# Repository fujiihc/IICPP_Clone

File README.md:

# IICPP_Clone
Mark IIC+/++ Inspired Clone

## Overview
This goal of this project was to create a reasonably accurate "clone" of the Mesa Boogie Mark IIC+/++ Tube Amplifier. 
I was inspired by my love of Metallica and James Hetfield's rhythm playing, as well as my fascination with audio electronics.

These amplifiers can be considered legendary and are the subject of many discussions on what makes them so special and highly sought after.
Although a legitimate Mark IIC+ Reissue exists, as do many originals, these amps are often expensive, and vary in their component and feature choices.
I wouldn't consider this version to be a 100% perfect clone as there is not much accurate, detailed information on these amplifiers, and some of the schematics that are available have been noted to be incorrect. Certain components are also not readily available today, and so some design concessions have to be made. Modifications due to limited design information, component availability, limited budget, and design complexity were made. However, the core DNA and design choices of the original were followed as closely as possible and I  would consider this a reasonably faithful clone.
By having a more accessible, afforable, and reasonably accurate version, hopefully I can help contribute to others' tone chasing journeys, or help demystify (in some capacity) what makes these amps so special.

I currently do not own any Mesa Boogie amplifiers to base these designs off of. Instead, I have researched this amp in depth, scouring the internet for schematics, gut shots, and getting advice from others who have successfully built their own clones or similar amplifiers. 

A major goal of this project is to stay under a budget of $1800 (Half the price of a Reissue).

An important note, this project is for educational purposes and personal use only, and this repository is for documenting my learning progress and findings. I have no affiliation with Mesa Boogie or any sort of company or anything like that. I just like making stuff and playing guitar. Please don't sue me :)

## Table of Contents 
  **PROJECTS WERE CREATED IN KICAD 9.0**
  - [Custom Libraries](/Custom%20Libraries): Contains Custom Footprints for Parts Not Available from KICAD Default Libraries.
  - [Experiments](/Experiments): Contains Experimental Layouts and Ideas That Haven't Been Confirmed/Finalized.
  - [Graphic EQ](/Graphic%20EQ): Contains KICAD Projects with Schematics, PCB Designs, and Gerber Files for 5-Band EQ Driver and Slider Boards.
  - [Images](/Images): Contains Images for Various README's.
  - [Power Amp](/Power%20Amp): Contains KICAD Projects with Schematics, PCB Designs, and Gerber Files for Power Amp Boards.
  - [Power Supply](/Power%20Supply): Contains KICAD Projects with Schematics, PCB Designs, and Gerber Files for Power Supply Boards.
  - [Preamp](/Preamp): Contains KICAD Projects with Schematics, PCB Designs, and Gerber Files for Preamp Boards.

## Organizational/Research Spreadsheet
Contains Research Links, Bill of Materials, Instructions, Personal Findings, Notes, etc.
 - [Link to Google Sheet](https://docs.google.com/spreadsheets/d/1ZE0vuGfygjLFiTaHai0WybOM6v7LY0qXNIPXHzz1JHo/edit?usp=sharing)

## Google Drive
Contains Pictures, Schematics, Datasheets, Manuals, Etc. Just useful information I found along the way.
 - [Link to Google Drive](https://drive.google.com/drive/folders/1geqLoLI9ncoWVvD1H8Yl4hjtfwfBTIB6?usp=drive_link)

## Thank You's
The following people have been invaluable in the progress of this project, both directly and indirectly. Whether they posted schematics that they traced, or in-depth gut shots or photos of their own builds, or even answered my questions when I ran into roadblocks, I would like to thank them. I wouldn't have made this much progress without them:

  - [JAY OMEGA](https://boogieforum.com/members/jay-omega.83481/)

  - [JRB32](https://boogieforum.com/members/jrb32.41252/)

  - [DANO](https://boogieforum.com/members/dan__o.6723/)

  - [DANN VALENTINO](https://www.facebook.com/dann.valentino/)

  - [MATADOR](https://boogieforum.com/members/matador.84058/)

## To-Do/Future Plans

  - Create Modified C++ Compatible Preamp Board With Reverb
  - Create Modified C++ Compatible Preamp Board Without Reverb
  - Create Power Amp Board
  - Create Public Google Drive with Helpful Files (Pictures, Schematics, Datasheets, Manuals, Etc).

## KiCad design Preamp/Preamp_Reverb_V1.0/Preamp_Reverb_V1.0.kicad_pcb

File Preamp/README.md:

# Preamp

## Overview
The Preamp for the IICPP has two switchable modes, Clean and Lead. There are also various Pull-Potentiometer/Switch Activated modes for tone shaping. 

It's important to note that the Tone Stack for the IICPP comes after the First Gain Stage, and before all the Following Gain Stages.
An optional mod for the IICPP is the "C++" Mod, which adds a little bit more gain on tap. This is an optional mod, but also switchable when implemented.

There are two versions of the Preamp here, one which has Reverb (R) and one with No Reverb (NR). the Reverb, when implemented, is footswitchable. The No Reverb version uses one less 12AX7 Preamp Tube, and uses fewer components as well.
The rest of the components and the schematic are the same.

## Status
  - 

## Bill Of Materials
  - [Link to Google Sheet](https://docs.google.com/spreadsheets/d/1ZE0vuGfygjLFiTaHai0WybOM6v7LY0qXNIPXHzz1JHo/edit?gid=1339717624#gid=1339717624)

## Notes
  - 
## To-Do/Future Plans
  - 
## Images

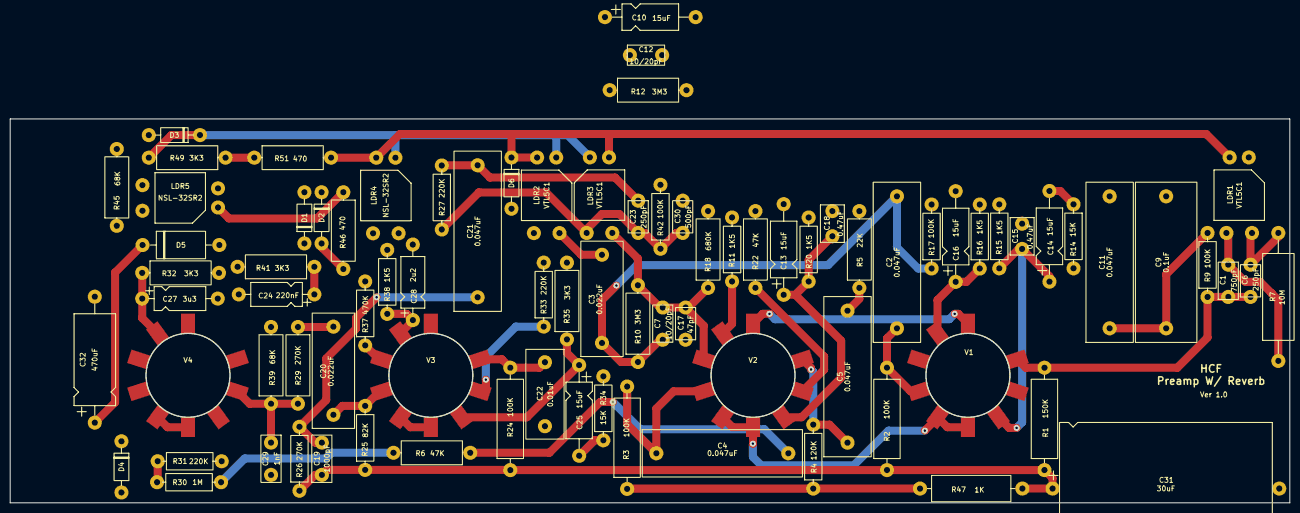
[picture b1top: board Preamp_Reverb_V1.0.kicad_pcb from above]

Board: 2 copper layers, 254.0 x 76.2 mm, 84 parts (0 on the bottom side), 47 nets.

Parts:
C1: 750pF; 20_750pF_1KV_Cer_7.4_4.0_.6.4
C2, C4, C5, C11, C21: 0.047uF; 715P47354LAD3
C3, C20: 0.022uF; 715P22354KAD3
C6, C23: 250pF; 10_47_120_180_250_500pF_1KV_Cer_6.4_4.0_6.4
C7, C12: 10/20pF; 20_750pF_1KV_Cer_7.4_4.0_.6.4
C9: 0.1uF; 715P10454LAD3
C10, C13, C14, C16, C25: 15uF; CP_Axial_L11.0mm_D5.0mm_P18.00mm_Horizontal
C15, C18: 0.47uF; C_Rect_L7.2mm_W4.5mm_P5.00mm_FKS2_FKP2_MKS2_MKP2
C17: 47pF; 10_47_120_180_250_500pF_1KV_Cer_6.4_4.0_6.4
C19: 1000pF; 1000pF_1KV_Cer_9.4_4.0_6.4
C22: 0.01uF; 715P10354JAD3
C24: 220nF; CP_Axial_L10.0mm_D4.5mm_P15.00mm_Horizontal
C27: 3u3; CP_Axial_L10.0mm_D4.5mm_P15.00mm_Horizontal
C28: 2u2; CP_Axial_L10.0mm_D4.5mm_P15.00mm_Horizontal
C29: 1nF; 1000pF_1KV_Cer_9.4_4.0_6.4
C30: 500pF; 10_47_120_180_250_500pF_1KV_Cer_6.4_4.0_6.4
C31: 30uF; CP_Axial_L42.0mm_D26.0mm_P45.00mm_Horizontal
C32: 470uF; CP_Axial_L18.0mm_D8.0mm_P25.00mm_Horizontal
D1, D6: 6V 1W; D_DO-41_SOD81_P10.16mm_Horizontal
D2, D3, D4: 1N4006; D_DO-41_SOD81_P10.16mm_Horizontal
D5: 1N5352BRL; D_DO-201_P15.24mm_Horizontal
LDR1, LDR2, LDR3: VTL5C1; PerkinElmer_VTL5C
LDR4, LDR5: NSL-32SR2; PerkinElmer_VTL5C
R1: 150K; R_Axial_DIN0516_L15.5mm_D5.0mm_P20.32mm_Horizontal
R2, R3, R24: 100K; R_Axial_DIN0516_L15.5mm_D5.0mm_P20.32mm_Horizontal
R4: 120K; R_Axial_DIN0309_L9.0mm_D3.2mm_P12.70mm_Horizontal
R5: 22K; R_Axial_DIN0414_L11.9mm_D4.5mm_P15.24mm_Horizontal
R6, R22: 47K; R_Axial_DIN0414_L11.9mm_D4.5mm_P15.24mm_Horizontal
R7: 10M; R_Axial_DIN0617_L17.0mm_D6.0mm_P25.40mm_Horizontal
R9, R17, R42: 100K; R_Axial_DIN0309_L9.0mm_D3.2mm_P12.70mm_Horizontal
R10, R12: 3M3; R_Axial_DIN0414_L11.9mm_D4.5mm_P15.24mm_Horizontal
R11, R15, R16, R20, R38: 1K5; R_Axial_DIN0309_L9.0mm_D3.2mm_P12.70mm_Horizontal
R14, R34: 15K; R_Axial_DIN0309_L9.0mm_D3.2mm_P12.70mm_Horizontal
R18: 680K; R_Axial_DIN0414_L11.9mm_D4.5mm_P15.24mm_Horizontal
R25: 82K; R_Axial_DIN0309_L9.0mm_D3.2mm_P12.70mm_Horizontal
R26: 270K; R_Axial_DIN0309_L9.0mm_D3.2mm_P12.70mm_Horizontal
R27, R31, R33: 220K; R_Axial_DIN0309_L9.0mm_D3.2mm_P12.70mm_Horizontal
R29: 270K; R_Axial_DIN0414_L11.9mm_D4.5mm_P15.24mm_Horizontal
R30: 1M; R_Axial_DIN0309_L9.0mm_D3.2mm_P12.70mm_Horizontal
R32, R35, R41, R49: 3K3; R_Axial_DIN0414_L11.9mm_D4.5mm_P15.24mm_Horizontal
R37: 470K; R_Axial_DIN0309_L9.0mm_D3.2mm_P12.70mm_Horizontal
R39, R45: 68K; R_Axial_DIN0414_L11.9mm_D4.5mm_P15.24mm_Horizontal
R46, R51: 470; R_Axial_DIN0414_L11.9mm_D4.5mm_P15.24mm_Horizontal
R47: 1K; R_Axial_DIN0516_L15.5mm_D5.0mm_P20.32mm_Horizontal
V1, V2, V3, V4: 12AX7; VT9-ST-C

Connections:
D: R3.1, R4.1, R47.1
E: C19.1, C31.1, R1.1, R2.1, R24.1, R25.1, R26.1, R47.2
GEQ: LDR5.3, R45.1
GND: C15.2, C16.2, C17.2, C18.2, C27.2, C28.2, C29.2, C30.2, C31.2, C32.2, D1.2 (A), D5.2 (A), D6.2 (A), LDR4.3, LDR5.4, R11.2, R14.2, R15.2, R16.2, R17.2, R18.2, R20.2, R22.2, R31.2, R32.2, R33.2, R34.2, R35.2, R37.2, R38.2, R39.2, R41.2, R42.2, R45.2
LDR1+: D6.1 (K), LDR1.2 (+), LDR2.2 (+), LDR3.2 (+), LDR4.2 (+), R51.2
LDR2-: D3.1 (K), LDR2.1 (-), LDR3.1 (-), LDR4.1 (-), R49.2
Lead In: C3.2, LDR2.3
Lead Out: C7.2, C17.1, LDR3.4, R10.2, R18.1, V2.7 (G)
unnamed: C1.2, LDR1.4, R7.1
unnamed: C2.2, C3.1, C7.1, R10.1, R12.1, R17.1
unnamed: C4.2, R6.1
unnamed: C5.2, R5.1
unnamed: C6.2, LDR1.3, R7.2
unnamed: C9.1, C11.1, R9.2
unnamed: C12.1, R12.2
unnamed: C20.2, R29.1
unnamed: C21.2, C23.1, R27.1
unnamed: C23.2, C30.1, LDR3.3, R27.2, R42.1
unnamed: C25.2, R34.1
unnamed: D1.1 (K), LDR5.2 (+)
unnamed: D2.2 (A), R46.2
unnamed: C32.1, D5.1 (K), R49.1, R51.1
unnamed: LDR5.1 (-), R46.1
unnamed: C14.2, R14.1
unnamed: C2.1, R2.2, V1.6 (A)
unnamed: C16.1, R16.1, V1.8 (K)
unnamed: C1.1, C6.1, R1.2, R9.1, V1.1 (A)
unnamed: C14.1, C15.1, R15.1, V1.3 (K)
unnamed: V1.4 (F1), V1.5 (F1), V2.4 (F1), V2.5 (F1), V3.4 (F1), V3.5 (F1), V4.4 (F1), V4.5 (F1)
unnamed: V1.9 (F2), V2.9 (F2), V3.9 (F2), V4.9 (F2)
unnamed: C4.1, R3.2, V2.6 (A)
unnamed: C10.1, R11.1, V2.8 (K)
unnamed: C5.1, R4.2, V2.1 (A)
unnamed: R22.1, V2.2 (G)
unnamed: C13.1, C18.1, R20.1, V2.3 (K)
unnamed: C20.1, R25.2, V3.6 (A)
unnamed: R37.1, V3.7 (G)
unnamed: C28.1, R38.1, V3.8 (K)
unnamed: C22.1, R24.2, V3.1 (A)
unnamed: C25.1, R35.1, V3.3 (K)
unnamed: R30.2, R31.1, V4.7 (G)
unnamed: C27.1, R32.1, V4.8 (K)
unnamed: C19.2, C21.1, R26.2, V4.1 (A)
unnamed: C29.1, R29.2, R39.1, V4.2 (G)
unnamed: C24.1, R41.1, V4.3 (K)
Reverb In: R6.2, R30.1
Tank Out: R33.1, V3.2 (G)

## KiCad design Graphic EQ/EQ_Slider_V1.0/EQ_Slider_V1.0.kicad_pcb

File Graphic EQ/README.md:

# Graphic EQ

## Overview
The 5-Band Graphic Equalizer for the IICPP consists of two parts, the EQ Driver and the EQ Slider Board. 

In conjunction, they can boost or cut frequencies at 80Hz, 240Hz, 750Hz, 2200Hz and 6600Hz.

The GEQ can be engaged in EQ Out, EQ In, and EQ Auto Modes, and can be footswitched.

EQ Out has the GEQ Off, EQ In has the GEQ In for Lead and Clean Modes, and EQ Auto engages the EQ when Lead is engaged.

## Status
  - Schematics, PCB Designs, and Gerbers for V1.0 of both the Driver and Slider Boards are Complete.
  - Gerbers generated for JLCPCB Manufacturing.

## Bill Of Materials
  - [Link to Google Sheet](https://docs.google.com/spreadsheets/d/1ZE0vuGfygjLFiTaHai0WybOM6v7LY0qXNIPXHzz1JHo/edit?gid=0#gid=0)

## Notes
  - MPSA70 is discontinued.
    - Options are NOS, finding drop-in replacement, or finding suitable alternatives for ALL transistors.
  - T322/T110 Tantalum Caps are expensive.
    - T322/T110 were used in some originals, but Cheaper Tant Caps (T356), Film Caps, or Orange Drop Caps also apparently work.
    
## To-Do/Future Plans
  - Order V1.0 Boards
  - Find Suitable Transistor Replacements

## Images
Slider V1.0:

Driver V1.0:

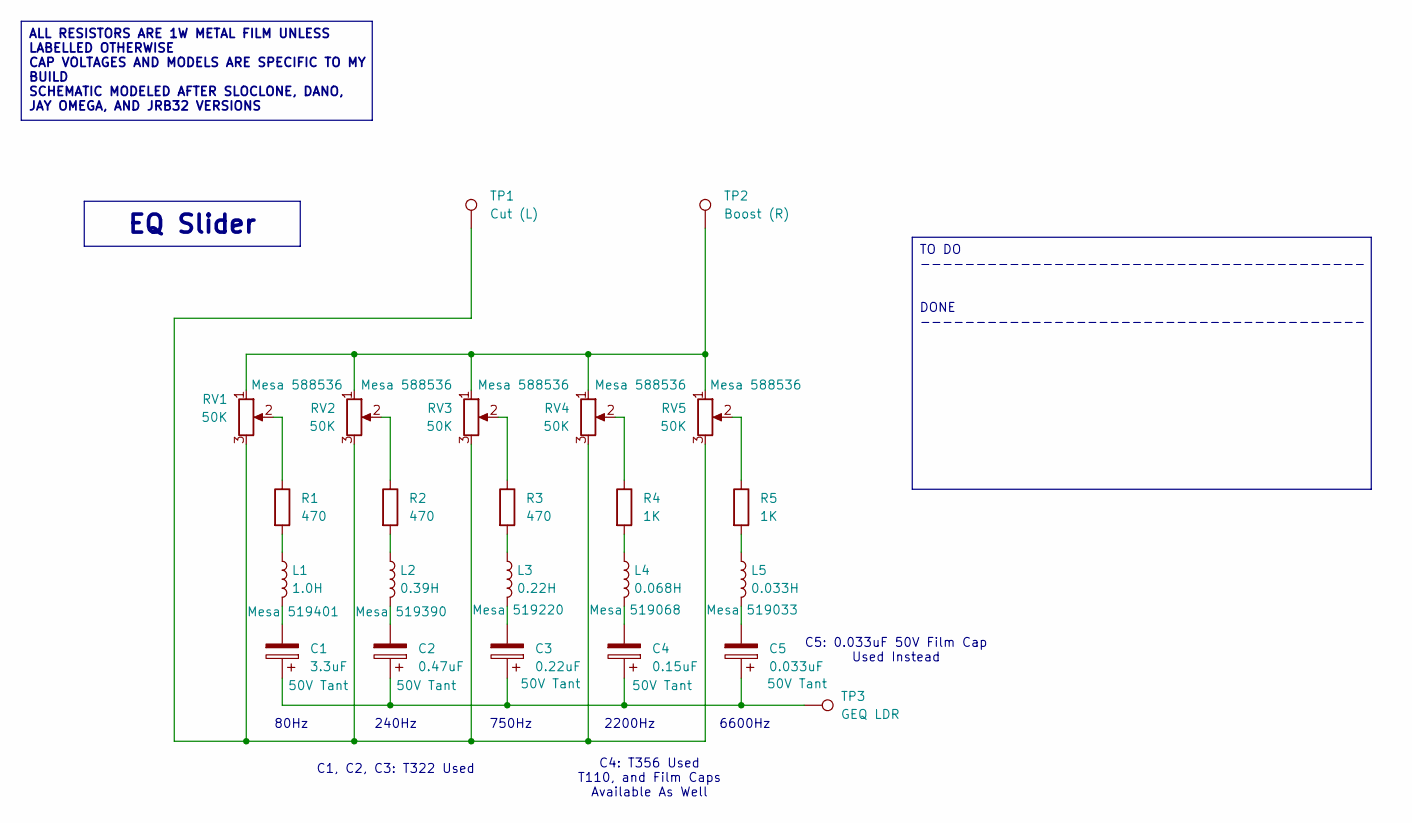
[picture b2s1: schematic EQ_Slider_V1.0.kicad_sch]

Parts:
C1: 3.3uF; CP_Axial_L11.0mm_D5.0mm_P18.00mm_Horizontal
C2: 0.47uF; CP_Axial_L10.0mm_D4.5mm_P15.00mm_Horizontal
C3: 0.22uF; CP_Axial_L10.0mm_D4.5mm_P15.00mm_Horizontal
C4: 0.15uF; CP_Radial_Tantal_D4.5mm_P5.00mm
C5: 0.033uF; C_Rect_L7.2mm_W2.5mm_P5.00mm_FKS2_FKP2_MKS2_MKP2
L1: 1.0H; MB Inductor
L2: 0.39H; MB Inductor
L3: 0.22H; MB Inductor
L4: 0.068H; MB Inductor
L5: 0.033H; MB Inductor
R1, R2, R3: 470; R_Axial_DIN0414_L11.9mm_D4.5mm_P15.24mm_Horizontal
R4, R5: 1K; R_Axial_DIN0414_L11.9mm_D4.5mm_P15.24mm_Horizontal
RV1, RV2, RV3, RV4, RV5: 50K; Mesa 588536
TP1: Cut (L); Out_Hole_3.4_1.8
TP2: Boost (R); Out_Hole_3.4_1.8
TP3: GEQ LDR; Out_Hole_3.4_1.8

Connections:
unnamed: C1.1, C2.1, C3.1, C4.1, C5.1, TP3.1
unnamed: C1.2, L1.2
unnamed: C2.2, L2.2
unnamed: C3.2, L3.2
unnamed: C4.2, L4.2
unnamed: C5.2, L5.2
unnamed: L1.1, R1.2
unnamed: L2.1, R2.2
unnamed: L3.1, R3.2
unnamed: L4.1, R4.2
unnamed: L5.1, R5.2
unnamed: R1.1, RV1.2
unnamed: R2.1, RV2.2
unnamed: R3.1, RV3.2
unnamed: R4.1, RV4.2
unnamed: R5.1, RV5.2
unnamed: RV1.1, RV2.1, RV3.1, RV4.1, RV5.1, TP2.1
unnamed: RV1.3, RV2.3, RV3.3, RV4.3, RV5.3, TP1.1

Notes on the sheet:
C5: 0.033uF 50V Film Cap Used Instead
750Hz
80Hz
240Hz
6600Hz
C4: T356 Used T110, and Film Caps Available As Well
2200Hz
C1, C2, C3: T322 Used
ALL RESISTORS ARE 1W METAL FILM UNLESS LABELLED OTHERWISE CAP VOLTAGES AND MODELS ARE SPECIFIC TO MY BUILD SCHEMATIC MODELED AFTER SLOCLONE, DANO, JAY OMEGA, AND JRB32 VERSIONS
TO DO ---------------------------------------- DONE ----------------------------------------
EQ Slider

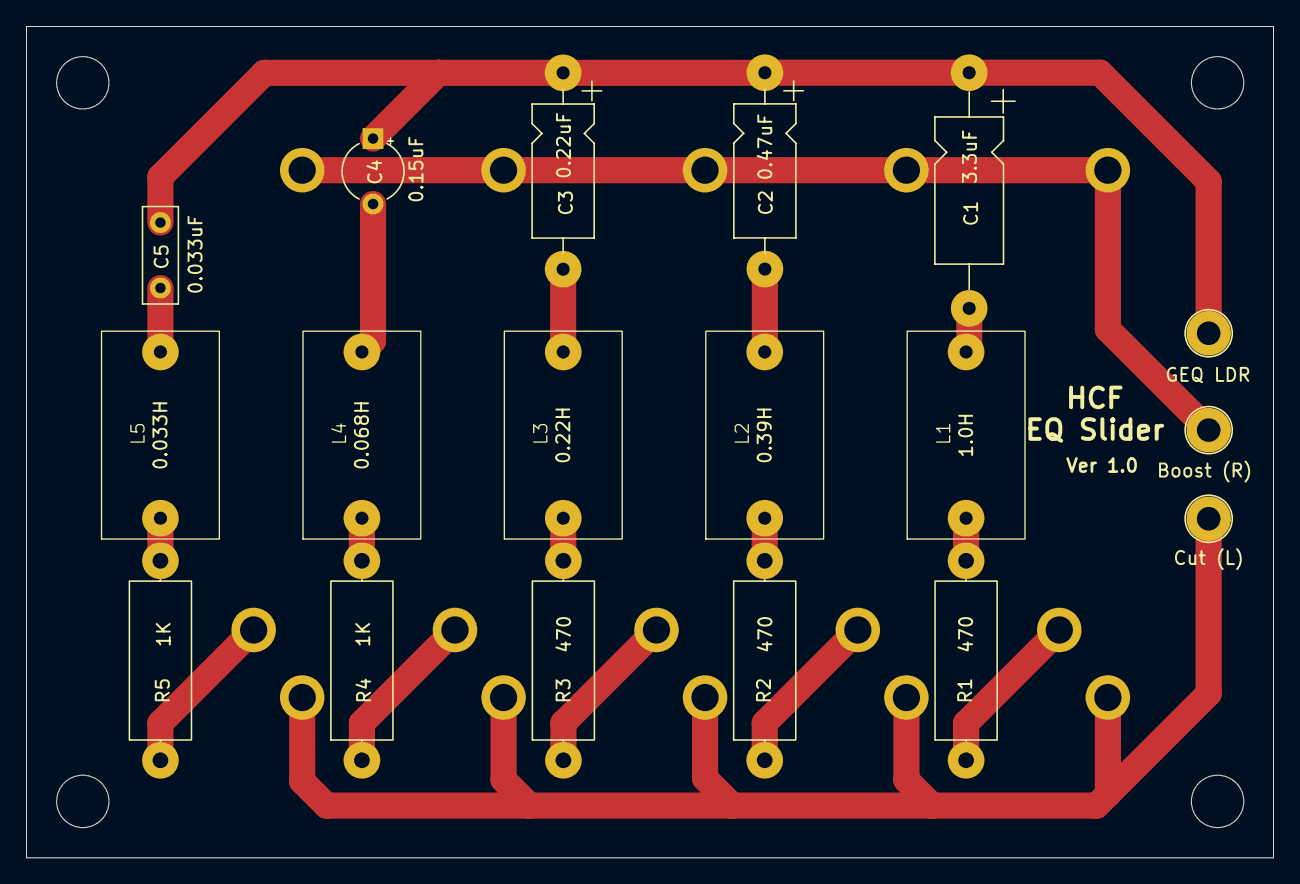
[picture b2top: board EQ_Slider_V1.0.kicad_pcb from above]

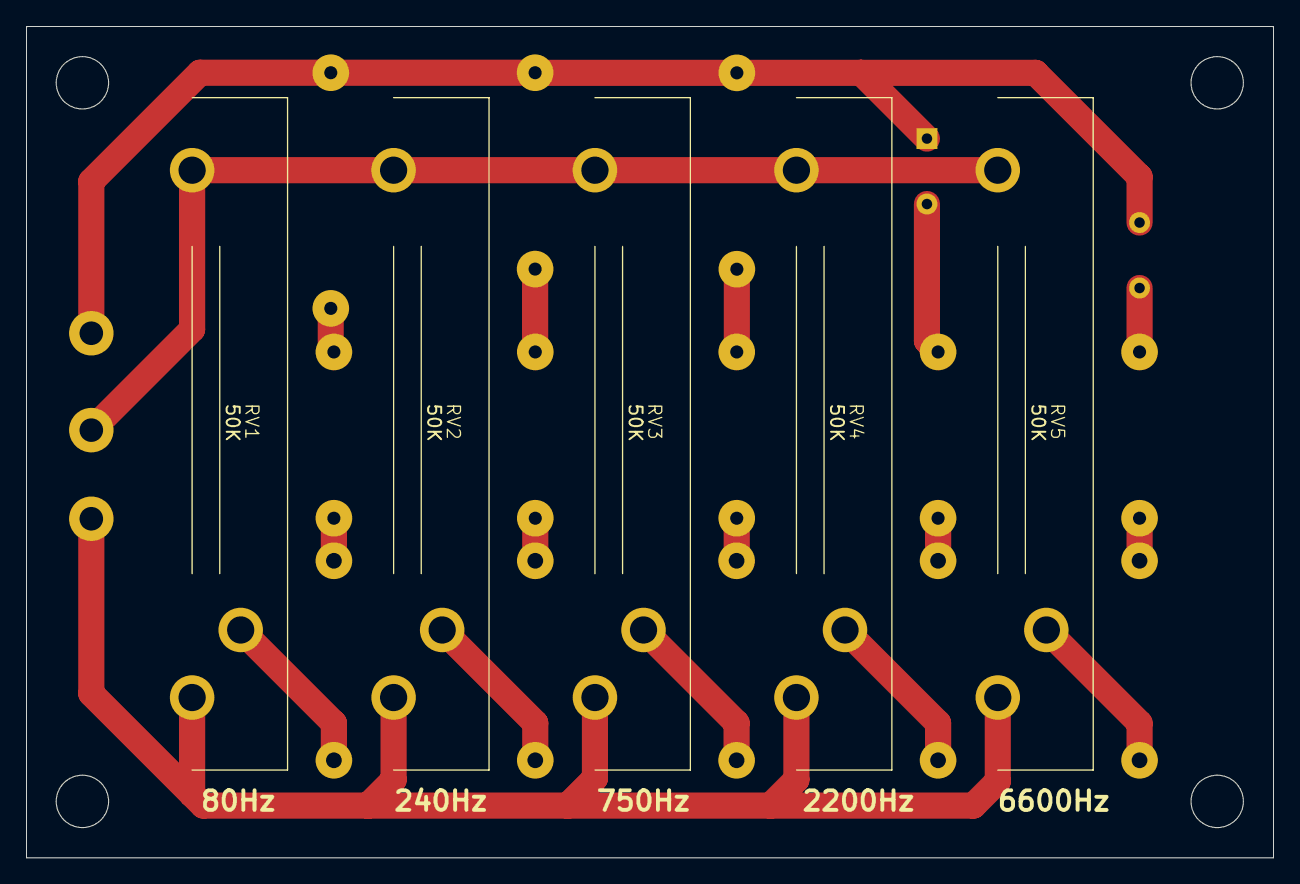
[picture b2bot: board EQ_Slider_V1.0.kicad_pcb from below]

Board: 2 copper layers, 95.3 x 63.5 mm, 23 parts (5 on the bottom side), 18 nets.

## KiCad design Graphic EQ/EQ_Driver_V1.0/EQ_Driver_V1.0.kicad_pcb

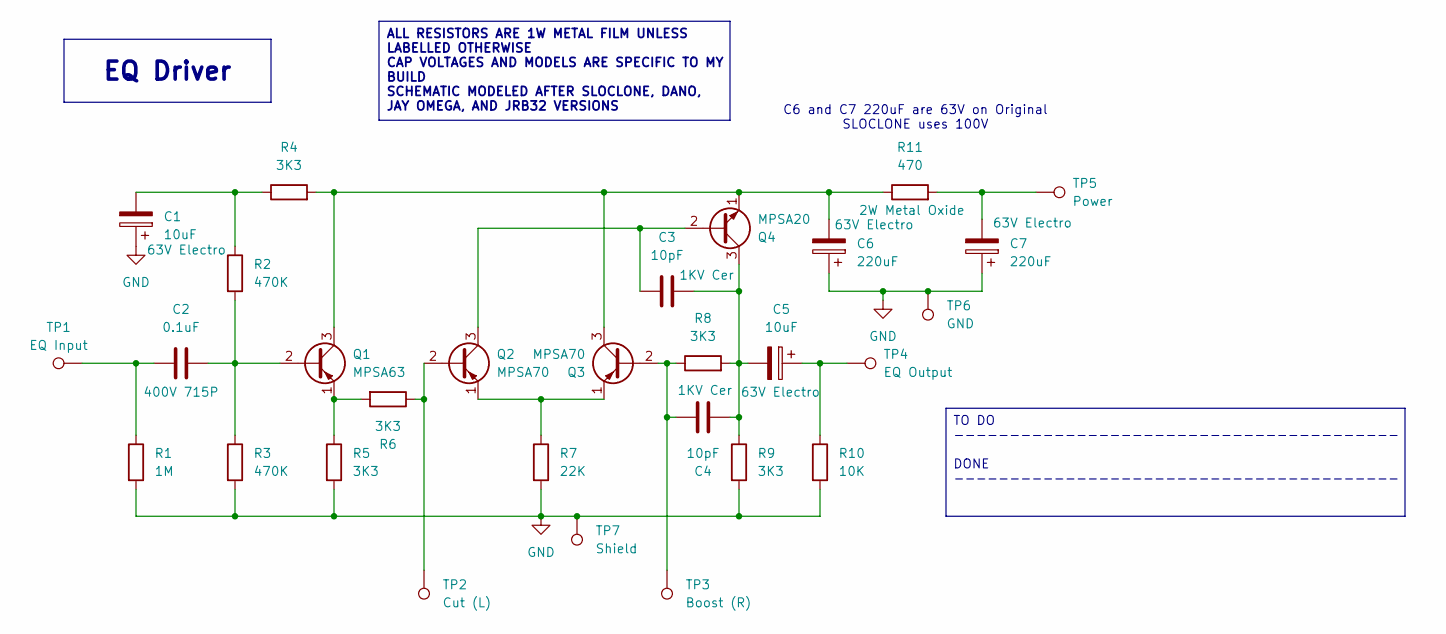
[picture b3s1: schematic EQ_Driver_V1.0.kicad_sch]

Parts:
C1, C5: 10uF; CP_Axial_L18.0mm_D6.5mm_P25.00mm_Horizontal
C2: 0.1uF; 715P10454LAD3
C3, C4: 10pF; 10_47_120_180_250_500pF_1KV_Cer_6.4_4.0_6.4
C6, C7: 220uF; CP_Axial_L25.0mm_D10.0mm_P30.00mm_Horizontal
Q1: MPSA63; TO-92_Wide
Q2, Q3: MPSA70; TO-92_Wide
Q4: MPSA20; TO-92_Wide
R1: 1M; R_Axial_DIN0309_L9.0mm_D3.2mm_P12.70mm_Horizontal
R2, R3: 470K; R_Axial_DIN0309_L9.0mm_D3.2mm_P12.70mm_Horizontal
R4, R5, R6, R8, R9: 3K3; R_Axial_DIN0414_L11.9mm_D4.5mm_P15.24mm_Horizontal
R7: 22K; R_Axial_DIN0414_L11.9mm_D4.5mm_P15.24mm_Horizontal
R10: 10K; R_Axial_DIN0309_L9.0mm_D3.2mm_P12.70mm_Horizontal
R11: 470; R_Axial_DIN0516_L15.5mm_D5.0mm_P20.32mm_Horizontal
TP1: EQ Input; WirePad
TP2: Cut (L); WirePad
TP3: Boost (R); WirePad
TP4: EQ Output; Out_Hole_3.4_1.8
TP5: Power; Out_Hole_3.4_1.8
TP6: GND; WirePad
TP7: Shield; WirePad

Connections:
GND: C1.1, C6.1, C7.1, R1.2, R3.2, R5.2, R7.2, R9.2, R10.2, TP6.1, TP7.1
unnamed: C1.2, R2.1, R4.1
unnamed: C2.1, R1.1, TP1.1
unnamed: C5.1, R10.1, TP4.1
unnamed: C7.2, R11.2, TP5.1
unnamed: C2.2, Q1.2 (B), R2.2, R3.1
unnamed: C6.2, Q1.3 (C), Q3.3 (C), Q4.1 (E), R4.2, R11.1
unnamed: Q1.1 (E), R5.1, R6.2
unnamed: Q2.2 (B), R6.1, TP2.1
unnamed: C3.1, Q2.3 (C), Q4.2 (B)
unnamed: Q2.1 (E), Q3.1 (E), R7.1
unnamed: C4.1, Q3.2 (B), R8.1, TP3.1
unnamed: C3.2, C4.2, C5.2, Q4.3 (C), R8.2, R9.1

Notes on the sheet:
C6 and C7 220uF are 63V on Original SLOCLONE uses 100V
EQ Driver
ALL RESISTORS ARE 1W METAL FILM UNLESS LABELLED OTHERWISE CAP VOLTAGES AND MODELS ARE SPECIFIC TO MY BUILD SCHEMATIC MODELED AFTER SLOCLONE, DANO, JAY OMEGA, AND JRB32 VERSIONS
TO DO ---------------------------------------- DONE ----------------------------------------

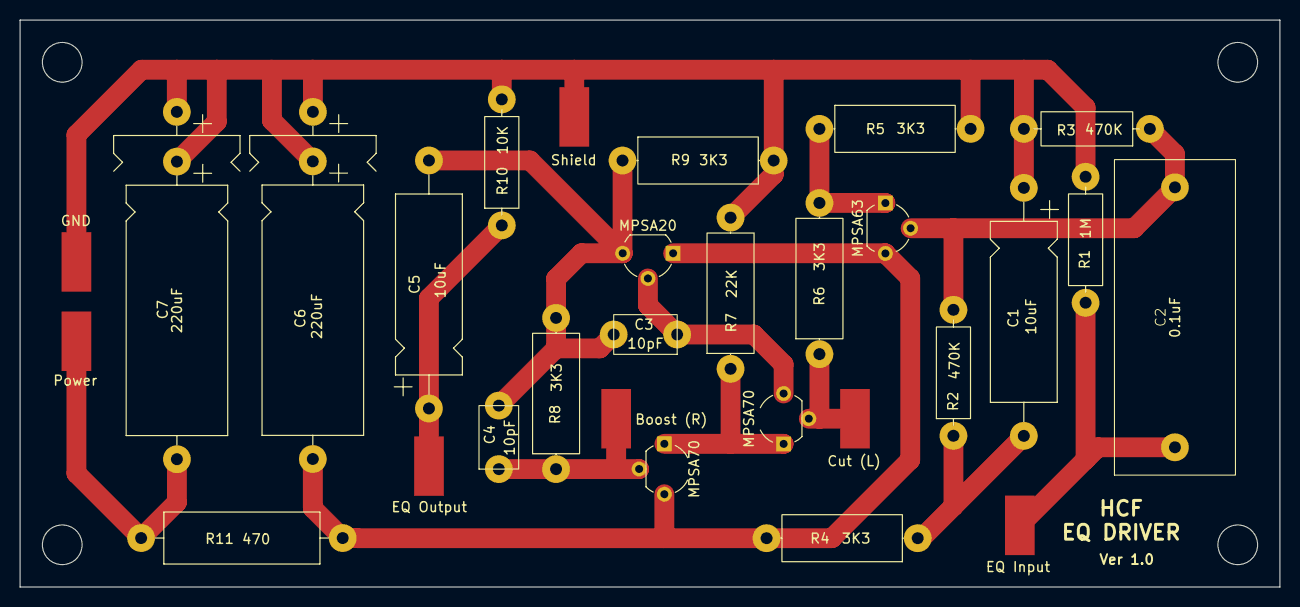
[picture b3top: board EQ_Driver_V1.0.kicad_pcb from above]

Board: 2 copper layers, 127.0 x 57.2 mm, 29 parts (0 on the bottom side), 13 nets.

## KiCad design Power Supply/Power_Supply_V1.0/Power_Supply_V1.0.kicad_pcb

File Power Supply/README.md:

# Power Supply

## Overview
The Power Supply for the IICPP contains the Main HT/B+ Taps as well as the Bias and Graphic EQ Power Supplies.

The board supports x2 (for 60W) and x4 (for 100W and Simul-Class) 300V 220uF Reservoir Caps.

## Status
  - Schematic, PCB Design, and Gerber for V1.0 of the Power Supply Board are Complete.
  - Gerbers generated for JLCPCB Manufacturing.

## Bill Of Materials
  - [Link to Google Sheet](https://docs.google.com/spreadsheets/d/1ZE0vuGfygjLFiTaHai0WybOM6v7LY0qXNIPXHzz1JHo/edit?gid=810989497#gid=810989497)

## Notes
  - Bias Supply for SLOCLONE/DANO, Mesa Boogie, and JRB32 Schematics are incorrect. The correct Bias Supply Schematic is used in this V1.0, which was traced from original IIB and IIC+ Power Supply Boards.
  - Validated/Correct and Incorrect Bias Supply Versions and Validation Sources can be found in [Experiments](../Experiments)
    
## To-Do/Future Plans
  - Add/Remove Taps based on Power Transformer. Currently looking at Hammond 291ZZ.

## Images
Power Supply V1.0:

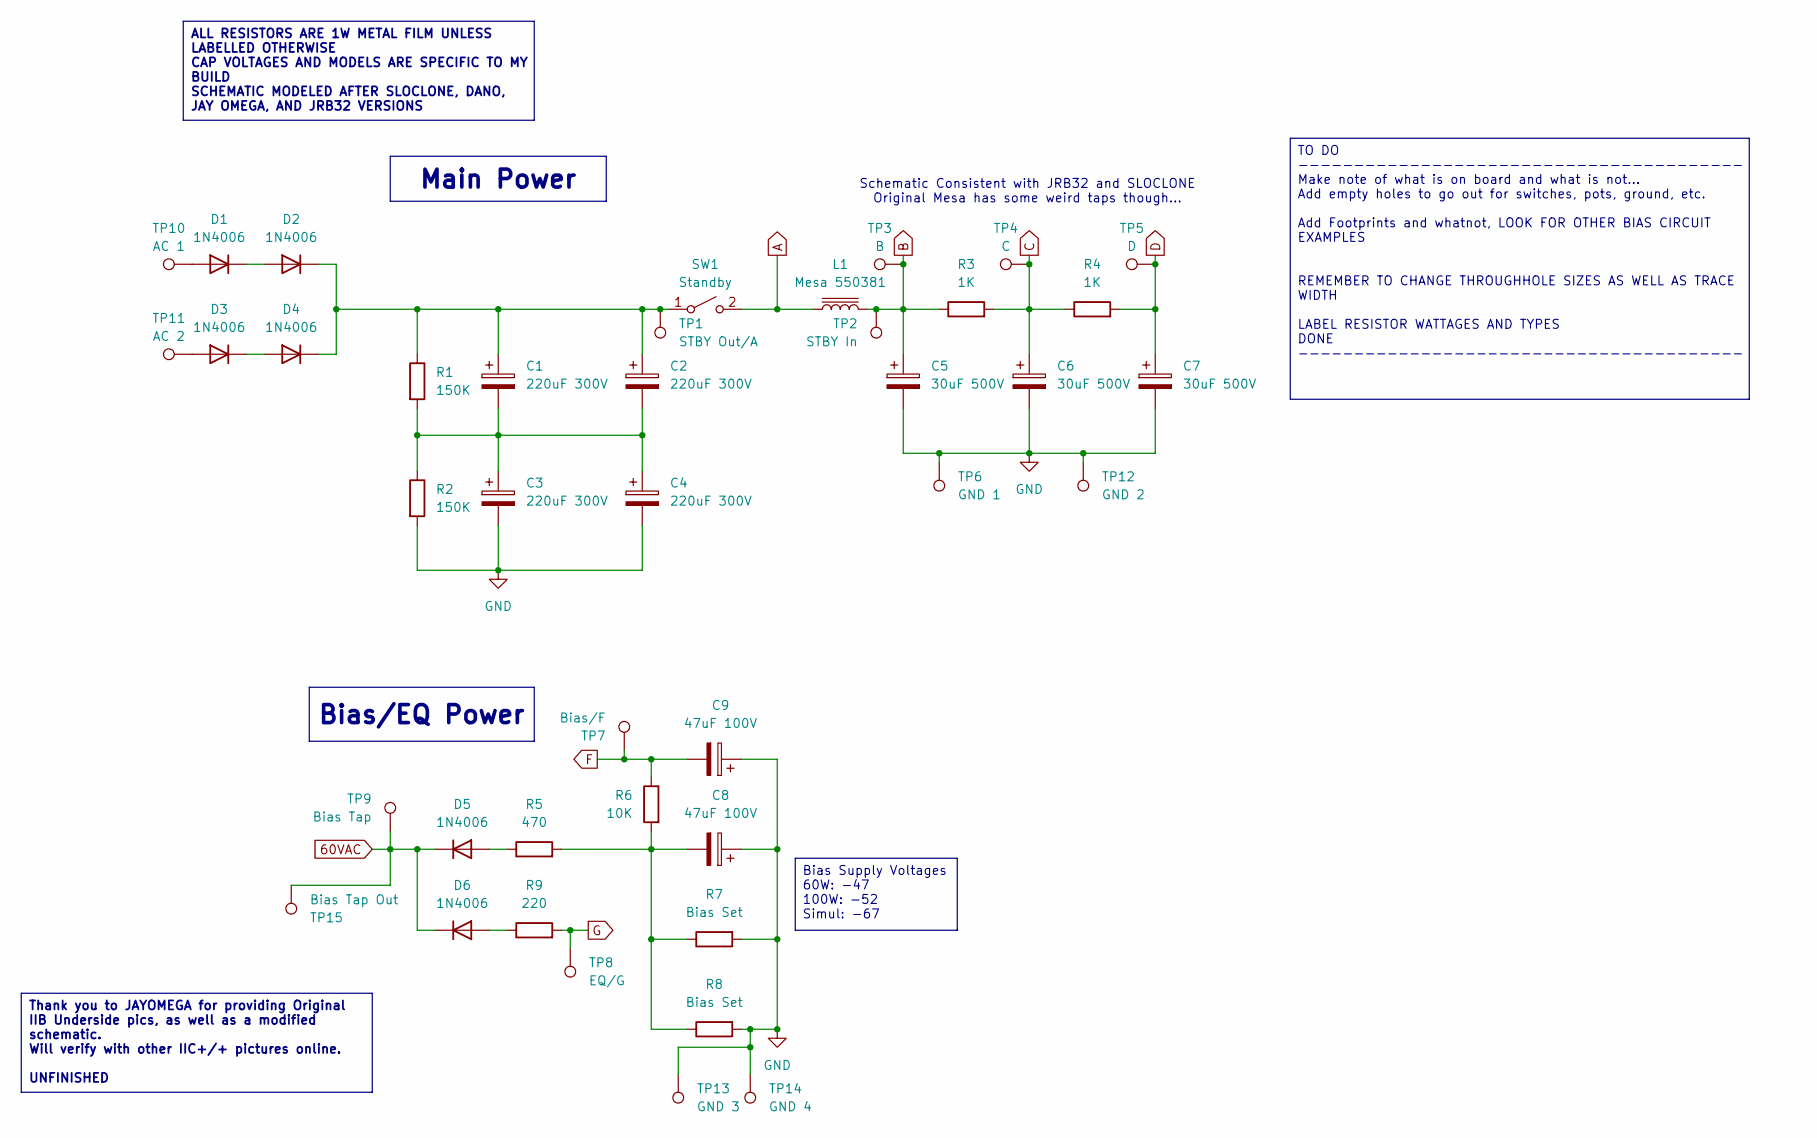
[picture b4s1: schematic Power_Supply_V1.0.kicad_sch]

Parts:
C1, C2, C3, C4: 220uF 300V; CP_Axial_L55.0mm_D26.0mm_P60.00mm_Horizontal
C5, C6, C7: 30uF 500V; CP_Axial_L42.0mm_D26.0mm_P45.00mm_Horizontal
C8, C9: 47uF 100V; CP_Axial_L18.0mm_D8.0mm_P25.00mm_Horizontal
D1, D2, D3, D4, D5, D6: 1N4006; D_DO-41_SOD81_P10.16mm_Horizontal
L1: Mesa 550381
R1, R2: 150K; R_Axial_DIN0516_L15.5mm_D5.0mm_P20.32mm_Horizontal
R3, R4: 1K; R_Axial_DIN0516_L15.5mm_D5.0mm_P20.32mm_Horizontal
R5: 470; R_Axial_DIN0516_L15.5mm_D5.0mm_P20.32mm_Horizontal
R6: 10K; R_Axial_DIN0309_L9.0mm_D3.2mm_P12.70mm_Horizontal
R7, R8: Bias Set; R_Axial_DIN0309_L9.0mm_D3.2mm_P12.70mm_Horizontal
R9: 220; R_Axial_DIN0516_L15.5mm_D5.0mm_P20.32mm_Horizontal
SW1: Standby
TP1: STBY Out/A; Out_Hole_3.4_1.8
TP2: STBY In; Out_Hole_3.4_1.8
TP3: B; WirePad
TP4: C; WirePad
TP5: D; WirePad
TP6: GND 1; WirePad
TP7: Bias/F; WirePad
TP8: EQ/G; WirePad
TP9: Bias Tap; Out_Hole_3.4_1.8
TP10: AC 1; Out_Hole_3.4_1.8
TP11: AC 2; Out_Hole_3.4_1.8
TP12: GND 2; WirePad
TP13: GND 3; WirePad
TP14: GND 4; WirePad
TP15: Bias Tap Out; WirePad

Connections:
60VAC: D5.1 (K), D6.1 (K), TP9.1, TP15.1
B: C5.1, L1.2, R3.1, TP2.1, TP3.1
C: C6.1, R3.2, R4.1, TP4.1
D: C7.1, R4.2, TP5.1
F: C9.2, R6.1, TP7.1
G: R9.2, TP8.1
GND: C3.2, C4.2, C5.2, C6.2, C7.2, C8.1, C9.1, R2.2, R7.2, R8.2, TP6.1, TP12.1, TP13.1, TP14.1
unnamed: C1.2, C2.2, C3.1, C4.1, R1.2, R2.1
unnamed: C8.2, R5.2, R6.2, R7.1, R8.1
unnamed: D1.2 (A), TP10.1
unnamed: D1.1 (K), D2.2 (A)
unnamed: C1.1, C2.1, D2.1 (K), D4.1 (K), R1.1, SW1.1 (A), TP1.1
unnamed: D3.2 (A), TP11.1
unnamed: D3.1 (K), D4.2 (A)
unnamed: D5.2 (A), R5.1
unnamed: D6.2 (A), R9.1
unnamed: L1.1, SW1.2 (B)

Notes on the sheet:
Schematic Consistent with JRB32 and SLOCLONE Original Mesa has some weird taps though...
Thank you to JAYOMEGA for providing Original IIB Underside pics, as well as a modified schematic. Will verify with other IIC+/+ pictures online. UNFINISHED
ALL RESISTORS ARE 1W METAL FILM UNLESS LABELLED OTHERWISE CAP VOLTAGES AND MODELS ARE SPECIFIC TO MY BUILD SCHEMATIC MODELED AFTER SLOCLONE, DANO, JAY OMEGA, AND JRB32 VERSIONS
Main Power
Bias/EQ Power
TO DO ---------------------------------------- Make note of what is on board and what is not... Add empty holes to go out for switches, pots, ground, etc. Add Footprints and whatnot, LOOK FOR OTHER BIAS CIRCUIT EXAMPLES REMEMBER TO CHANGE THROUGHHOLE SIZES AS WELL AS TRACE WIDTH LABEL RESISTOR WATT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
Bias Supply Voltages 60W: -47 100W: -52 Simul: -67

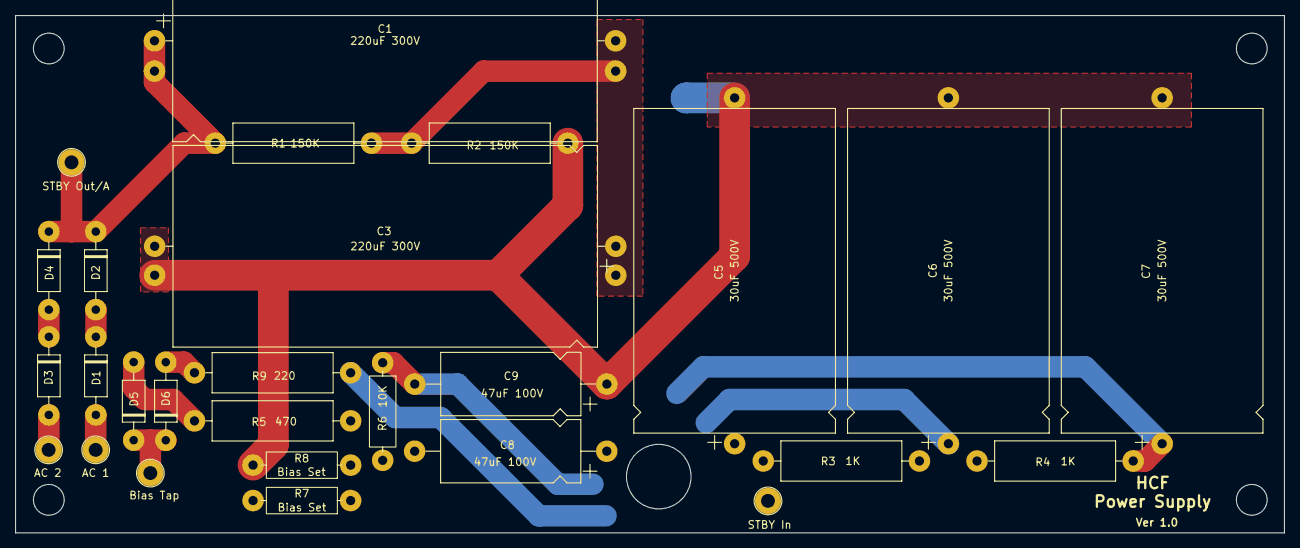
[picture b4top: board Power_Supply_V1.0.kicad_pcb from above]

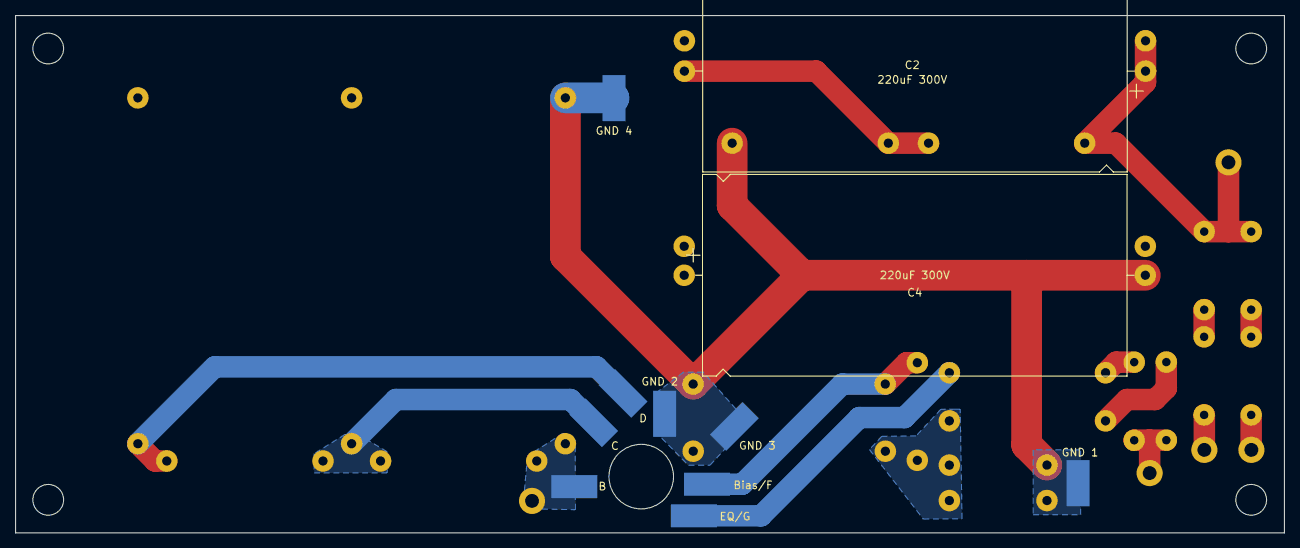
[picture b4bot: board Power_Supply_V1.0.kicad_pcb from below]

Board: 2 copper layers, 165.1 x 67.3 mm, 38 parts (11 on the bottom side), 16 nets.

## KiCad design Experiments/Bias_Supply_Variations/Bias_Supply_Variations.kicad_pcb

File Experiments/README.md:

# Experiments

## Overview
Sometimes, schematics found online are different from what was actually implemented on the original IIC+'s.
The experiments folder is to mock up schematic and layout variations, for later validation. 

## Status
  - Correct Bias Supply Validated

## Sources
  - Bias Supply
    - Source 1: Original IIB Underside
    - Source 2: Original IIC+ Underside
    
## To-Do/Future Plans
  -

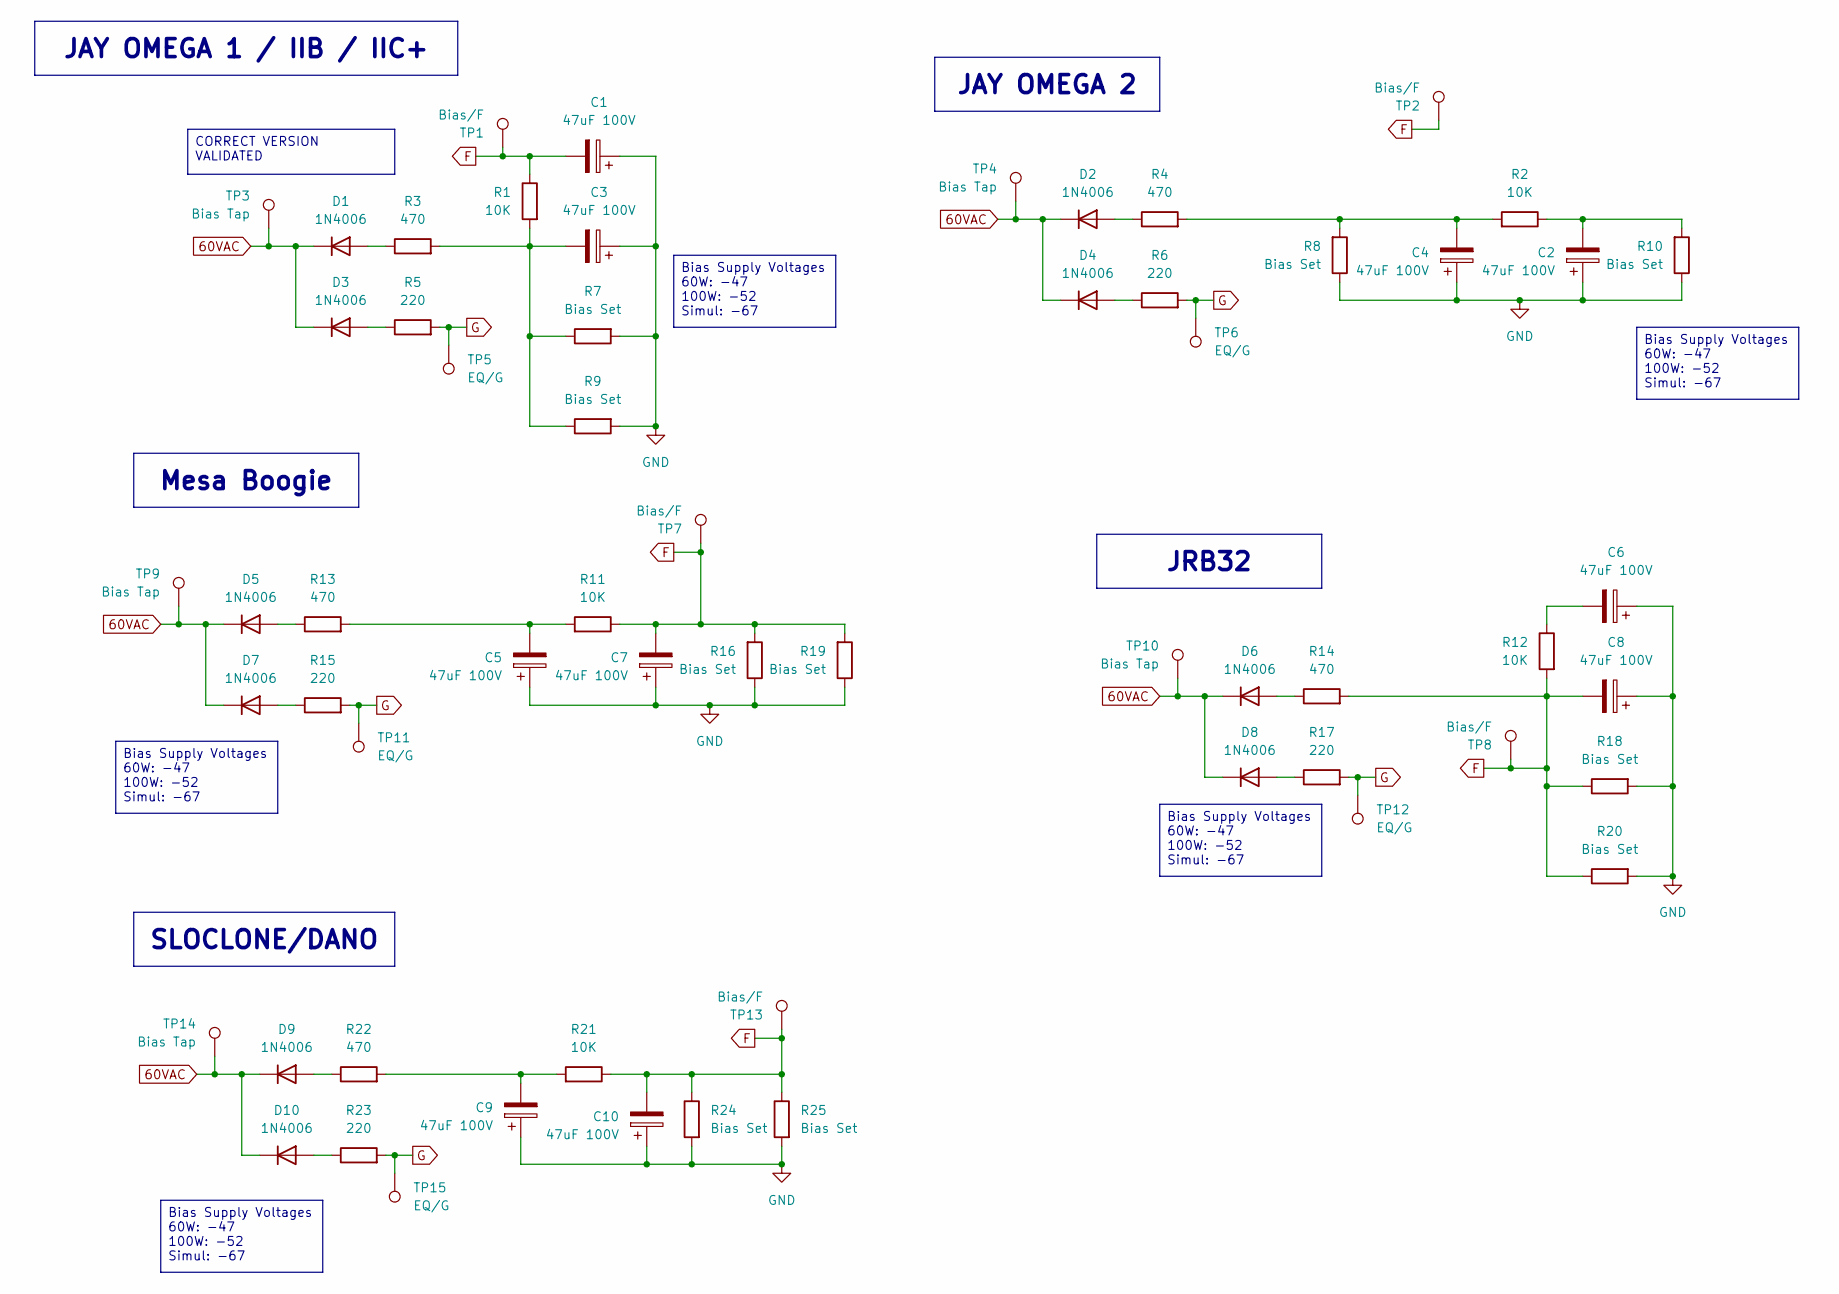
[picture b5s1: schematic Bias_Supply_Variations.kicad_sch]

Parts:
C1, C2, C3, C4, C5, C6, C7, C8, C9, C10: 47uF 100V; CP_Axial_L18.0mm_D8.0mm_P25.00mm_Horizontal
D1, D2, D3, D4, D5, D6, D7, D8, D9, D10: 1N4006; D_DO-41_SOD81_P10.16mm_Horizontal
R1, R2, R11, R12, R21: 10K; R_Axial_DIN0411_L9.9mm_D3.6mm_P15.24mm_Horizontal
R3, R4, R13, R14, R22: 470; R_Axial_DIN0516_L15.5mm_D5.0mm_P20.32mm_Horizontal
R5, R6, R15, R17, R23: 220; R_Axial_DIN0516_L15.5mm_D5.0mm_P20.32mm_Horizontal
R7, R8, R9, R10, R16, R18, R19, R20, R24, R25: Bias Set; R_Axial_DIN0411_L9.9mm_D3.6mm_P15.24mm_Horizontal
TP1, TP2, TP7, TP8, TP13: Bias/F; Out_Hole_3.4_1.8
TP3, TP4, TP9, TP10, TP14: Bias Tap; Out_Hole_3.4_1.8
TP5, TP6, TP11, TP12, TP15: EQ/G; Out_Hole_3.4_1.8

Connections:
60VAC: D1.1 (K), D2.1 (K), D3.1 (K), D4.1 (K), D5.1 (K), D6.1 (K), D7.1 (K), D8.1 (K), D9.1 (K), D10.1 (K), TP3.1, TP4.1, TP9.1, TP10.1, TP14.1
F: C1.2, C7.2, C8.2, C10.2, R1.1, R11.1, R12.2, R14.2, R16.2, R18.1, R19.2, R20.1, R21.1, R24.1, R25.1, TP1.1, TP2.1, TP7.1, TP8.1, TP13.1
G: R5.2, R6.2, R15.2, R17.2, R23.2, TP5.1, TP6.1, TP11.1, TP12.1, TP15.1
GND: C1.1, C2.1, C3.1, C4.1, C5.1, C6.1, C7.1, C8.1, C9.1, C10.1, R7.2, R8.1, R9.2, R10.1, R16.1, R18.2, R19.1, R20.2, R24.2, R25.2
unnamed: C2.2, R2.1, R10.2
unnamed: C3.2, R1.2, R3.2, R7.1, R9.1
unnamed: C4.2, R2.2, R4.2, R8.2
unnamed: C5.2, R11.2, R13.2
unnamed: C6.2, R12.1
unnamed: C9.2, R21.2, R22.2
unnamed: D1.2 (A), R3.1
unnamed: D2.2 (A), R4.1
unnamed: D3.2 (A), R5.1
unnamed: D4.2 (A), R6.1
unnamed: D5.2 (A), R13.1
unnamed: D6.2 (A), R14.1
unnamed: D7.2 (A), R15.1
unnamed: D8.2 (A), R17.1
unnamed: D9.2 (A), R22.1
unnamed: D10.2 (A), R23.1

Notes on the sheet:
Bias Supply Voltages 60W: -47 100W: -52 Simul: -67
Mesa Boogie
JAY OMEGA 1 / IIB / IIC+
SLOCLONE/DANO
JAY OMEGA 2
JRB32
CORRECT VERSION VALIDATED

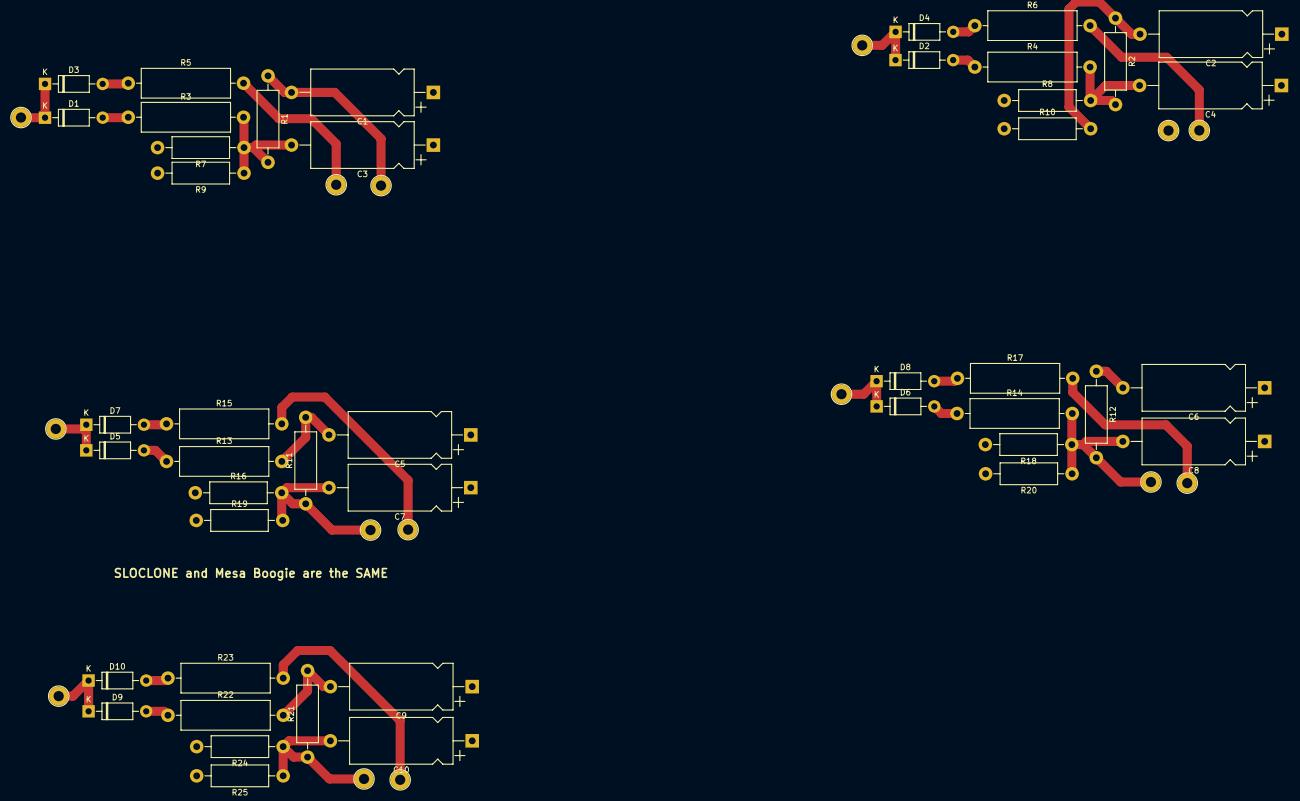
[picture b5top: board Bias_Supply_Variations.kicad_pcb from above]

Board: 2 copper layers, 60 parts (0 on the bottom side), 20 nets.

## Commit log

2025-04-08 Added First Schems
2025-04-08 Reannotated Schems
2025-04-08 Added Annotations
2025-04-24 Updated Schematics and Organizational Structure
2025-04-25 EQ Slider Board Progress
2025-04-25 Finished EQ Slider V1 Board
2025-04-25 organizational changes
2025-04-25 Added Images
2025-04-25 Added Comments to EQ Slider PCB
2025-04-27 Added EQ Driver/Slider V1.0 Gerbers
2025-04-28 Updated Driver V1.0 Gerber
2025-04-28 Updated V1.0 Driver Board
2025-04-29 Started Power Supply Board, Made EQ Driver Changes
2025-04-29 Power Supply Board Progress
2025-04-30 Completed Initial Mockup of Power Supply Board PCB
2025-04-30 Added Power Supply V1.0 Gerber
2025-04-30 organizational change
2025-05-01 Updated Gerber
2025-05-01 Condensed Reservoir Caps
2025-05-02 Added Bias Supply Experiments
2025-05-02 added Power Supply V1.0 Images
2025-05-02 Created Different Bias Schematics and Layout for Future Reference
2025-05-02 Validated Correct Bias Supply Schematic/Layout
2025-05-02 increased ground trace in PSV1.0
2025-05-04 Started Preamp Boards
2025-05-04 remove old versions of preamp layout
2025-05-10 Added test points to preamp board for layout planning
2025-05-11 Preamp Board Progress
2025-05-27 small updates
2025-05-27 Changed Driver Layout
2025-05-30 Added Solder Pads, Updated Power Supply Board
2025-05-30 Power Supply progress
2025-05-30 Made slider board more compact
2025-06-01 increased trace width
2025-06-01 updated power supply board with more diode spacing
2025-06-01 improved grounding trace size and scheme for power supply
2025-06-15 Updated Ceramic Capacitor Footprints
2025-06-16 Adjusted Resistor Sizes
2025-06-20 Preamp Progress, and Custom Footprint Library
2025-07-03 Updated 12AX7 footprint, resized preamp board
2025-07-05 initial Preamp Traces
2025-07-08 Preamp board progress, placed most of parts
